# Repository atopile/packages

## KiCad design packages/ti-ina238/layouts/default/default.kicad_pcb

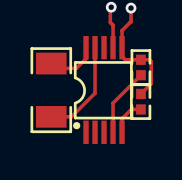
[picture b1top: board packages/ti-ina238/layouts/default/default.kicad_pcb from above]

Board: 2 copper layers, 4 parts (0 on the bottom side), 6 nets.

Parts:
R1: 80mΩ; R1206
R2, R3: 10kΩ; R0402
U1: VSSOP-10_L3.0-W3.0-P0.50-LS4.9-BL

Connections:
INneg_N: R1.2, U1.9
INpos_P: R1.1, U1.10
SCL: R2.1, U1.5
SDA: R3.1, U1.4
hv: R2.2, R3.2, U1.6
lv: U1.1, U1.2, U1.7

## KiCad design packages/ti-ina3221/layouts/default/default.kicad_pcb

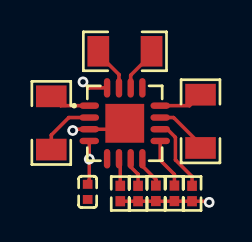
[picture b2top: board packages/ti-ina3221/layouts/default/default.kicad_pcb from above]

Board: 2 copper layers, 10 parts (0 on the bottom side), 13 nets.

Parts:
C1: 0F; C0402
R1, R2, R3: 0.15Ω; R1206
R4, R5, R6, R7, R8: 10000Ω; R0402
U1: QFN-16_L4.0-W4.0-P0.65-TL-EP2.2

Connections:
CRITICAL: R4.2, U1.9
PV: R7.2, U1.10
SCL: R5.2, U1.6
SDA: R6.2, U1.7
WARNING: R8.2, U1.8
channels[1]-power_in-power_in_P: R2.1, U1.15
channels[1]-power_out-power_out_N: R2.2, U1.14
channels[2]-power_in-power_in_P: R3.1, U1.2
channels[2]-power_out-power_out_N: R3.2, U1.1
hv: C1.1, R4.1, R5.1, R6.1, R7.1, R8.1, U1.4, U1.16
lv: C1.2, U1.3, U1.5, U1.17
power_in_P: R1.1, U1.12
power_out_N: R1.2, U1.11

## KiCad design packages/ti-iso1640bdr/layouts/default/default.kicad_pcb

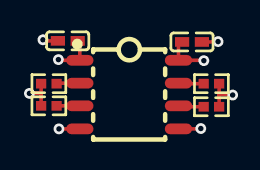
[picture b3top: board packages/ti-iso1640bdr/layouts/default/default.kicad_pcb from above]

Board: 2 copper layers, 7 parts (0 on the bottom side), 8 nets.

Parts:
C1, C2: 100nF ±10% 16V X7R; C0402
R1, R2, R3, R4: 10kΩ ±1% 62.5mW; R0402
U1: SOIC-8_L4.9-W3.9-P1.27-LS6.0-TL

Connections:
-gnd-0: C1.2, U1.4
-gnd-1: C2.2, U1.5
SCL1: R1.2, U1.3
SCL2: R2.2, U1.6
SDA1: R3.2, U1.2
SDA2: R4.2, U1.7
VCC1: C1.1, R1.1, R3.1, U1.1
VCC2: C2.1, R2.1, R4.1, U1.8

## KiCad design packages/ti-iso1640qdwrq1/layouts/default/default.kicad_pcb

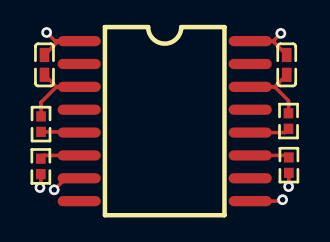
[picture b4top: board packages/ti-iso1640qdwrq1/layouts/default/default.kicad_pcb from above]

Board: 2 copper layers, 7 parts (0 on the bottom side), 8 nets.

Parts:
C1, C2: 100nF ±10% 16V X7R; C0402
R1, R2, R3, R4: 10kΩ ±1% 62.5mW; R0402
U1: SOIC-16_L10.3-W7.4-P1.27-LS10.3-BL

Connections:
i2cs[0]-SCL: R1.2, U1.6
i2cs[0]-SDA: R3.2, U1.5
i2cs[1]-SCL: R2.2, U1.11
i2cs[1]-SDA: R4.2, U1.12
power_rails[0]-GND: C1.2, U1.1, U1.7
power_rails[0]-VCC: C1.1, R1.1, R3.1, U1.3
power_rails[1]-GND: C2.2, U1.9, U1.16
power_rails[1]-VCC: C2.1, R2.1, R4.1, U1.14
